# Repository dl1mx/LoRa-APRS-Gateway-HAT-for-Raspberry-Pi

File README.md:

What is it?
-----------
With this LoRa APRS board you can build a LoRa APRS single channel Gateway with RA-01.  
The Board is based on the development of https://www.lora-aprs.at/ and http://www.iot4pi.com/  
It works with a Raspberry Pi (2 Model B, 3 Model B an B+, Zero WH).  
Power is provided by Raspberry Pi.

What you find here
------------------
- KiCad Fils
- Gerber Files
- Manuals
- Pictures of the LoRa-APRS-Board

Info & Software
---------------
You find information and Software for the LoRa-APRS Gateway at  
https://www.aronaut.at/2019/11/lora-aprs-gateway-fur-raspberry-pi/  
https://www.lora-aprs.at/  
http://www.iot4pi.com/de/hardware/lora-gateway/  
https://github.com/tomelec/RPi-LoRa-KISS-TNC

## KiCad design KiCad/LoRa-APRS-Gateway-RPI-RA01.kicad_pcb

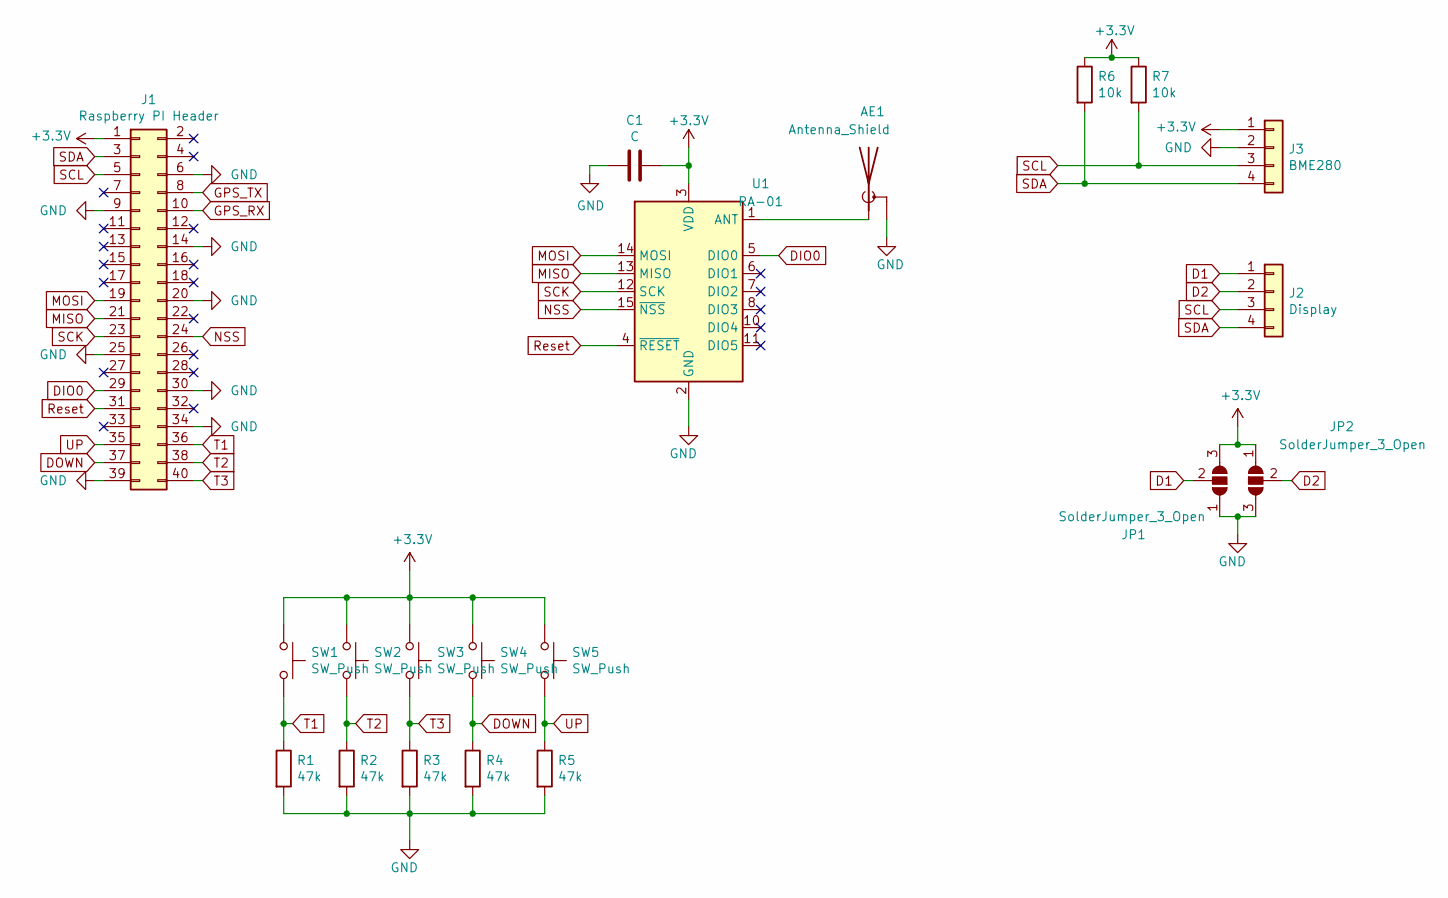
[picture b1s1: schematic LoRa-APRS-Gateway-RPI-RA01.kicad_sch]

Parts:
AE1: Antenna_Shield; SMA_Amphenol_901-144_Vertical
C1: C; C_0805_2012Metric
J1: Raspberry PI Header; PinSocket_2x20_P2.54mm_Vertical
J2: Display; OLED_0,96_II
J3: BME280; PinHeader_1x04_P2.54mm_Vertical
JP1, JP2: SolderJumper_3_Open; SolderJumper-3_P1.3mm_Open_Pad1.0x1.5mm
R1, R2, R3, R4, R5: 47k; R_Axial_DIN0207_L6.3mm_D2.5mm_P7.62mm_Horizontal
R6, R7: 10k; R_Axial_DIN0207_L6.3mm_D2.5mm_P7.62mm_Horizontal
SW1, SW2, SW3, SW4, SW5: SW_Push; SW_PUSH_6mm_H5mm
U1: RA-01; Ai-Thinker-Ra-01-LoRa

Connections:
+3.3V: C1.1, J1.1, J3.1, JP1.3 (B), JP2.1 (A), R6.1, R7.1, SW1.1, SW2.1, SW3.1, SW4.1, SW5.1, U1.3 (VDD)
D1: J2.1, JP1.2 (C)
D2: J2.2, JP2.2 (C)
DIO0: J1.29, U1.5 (DIO0)
DOWN: J1.37, R4.1, SW4.2
GND: AE1.2 (Shield), C1.2, J1.6, J1.9, J1.14, J1.20, J1.25, J1.30, J1.34, J1.39, J3.2, JP1.1 (A), JP2.3 (B), R1.2, R2.2, R3.2, R4.2, R5.2, U1.2 (GND), U1.9 (GND), U1.16 (GND)
GPS_RX: J1.10
GPS_TX: J1.8
MISO: J1.21, U1.13 (MISO)
MOSI: J1.19, U1.14 (MOSI)
NSS: J1.24, U1.15 (~NSS)
unnamed: AE1.1 (A), U1.1 (ANT)
Reset: J1.31, U1.4 (~RESET)
SCK: J1.23, U1.12 (SCK)
SCL: J1.5, J2.3, J3.3, R7.2
SDA: J1.3, J2.4, J3.4, R6.2
T1: J1.36, R1.1, SW1.2
T2: J1.38, R2.1, SW2.2
T3: J1.40, R3.1, SW3.2
UP: J1.35, R5.1, SW5.2

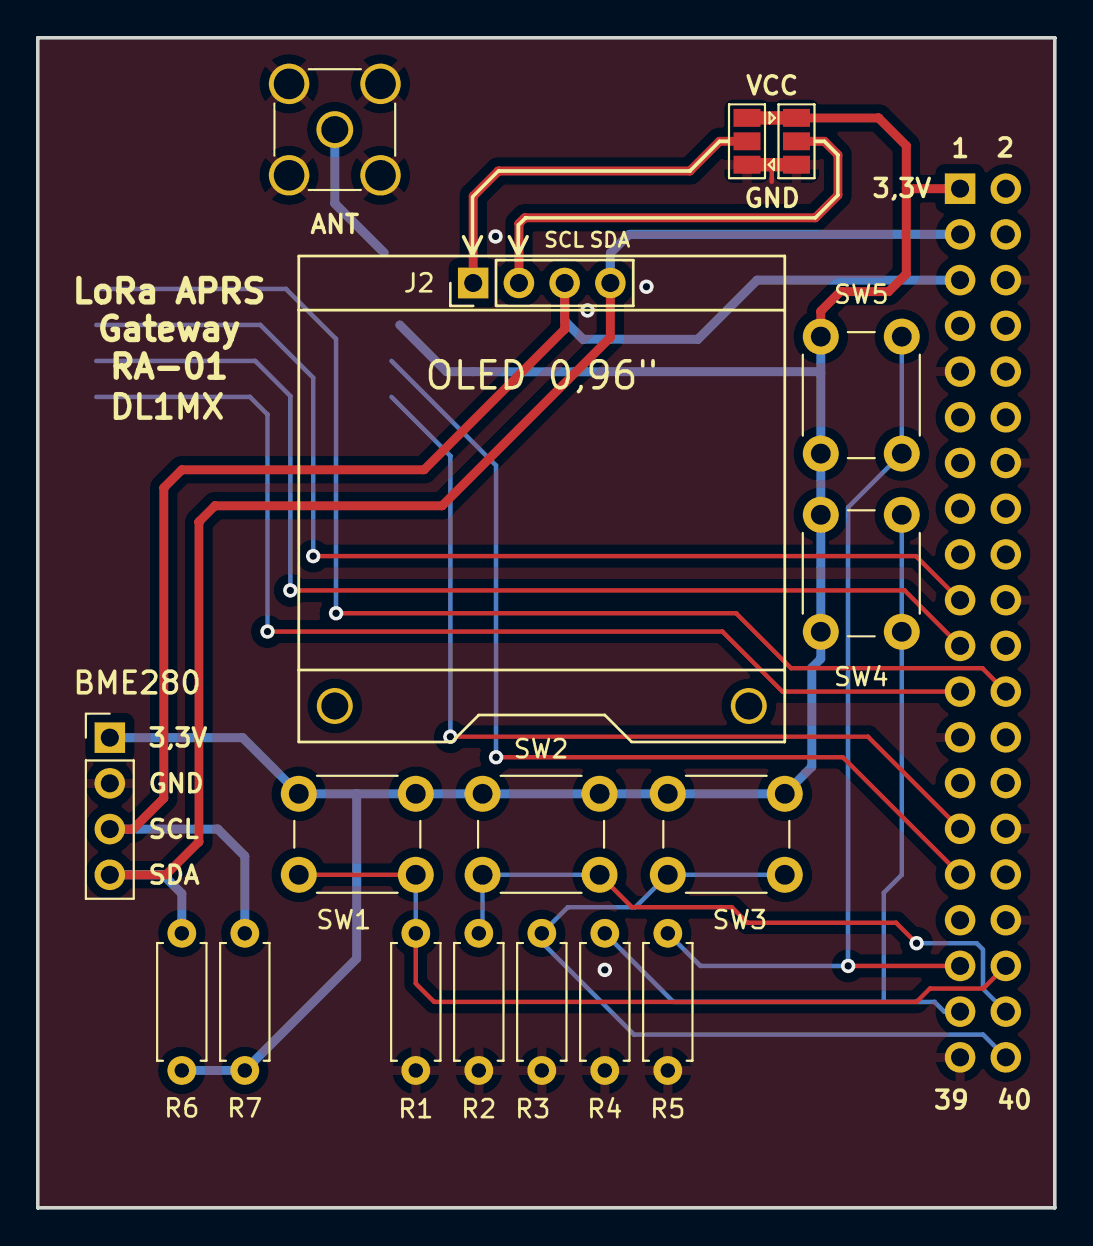
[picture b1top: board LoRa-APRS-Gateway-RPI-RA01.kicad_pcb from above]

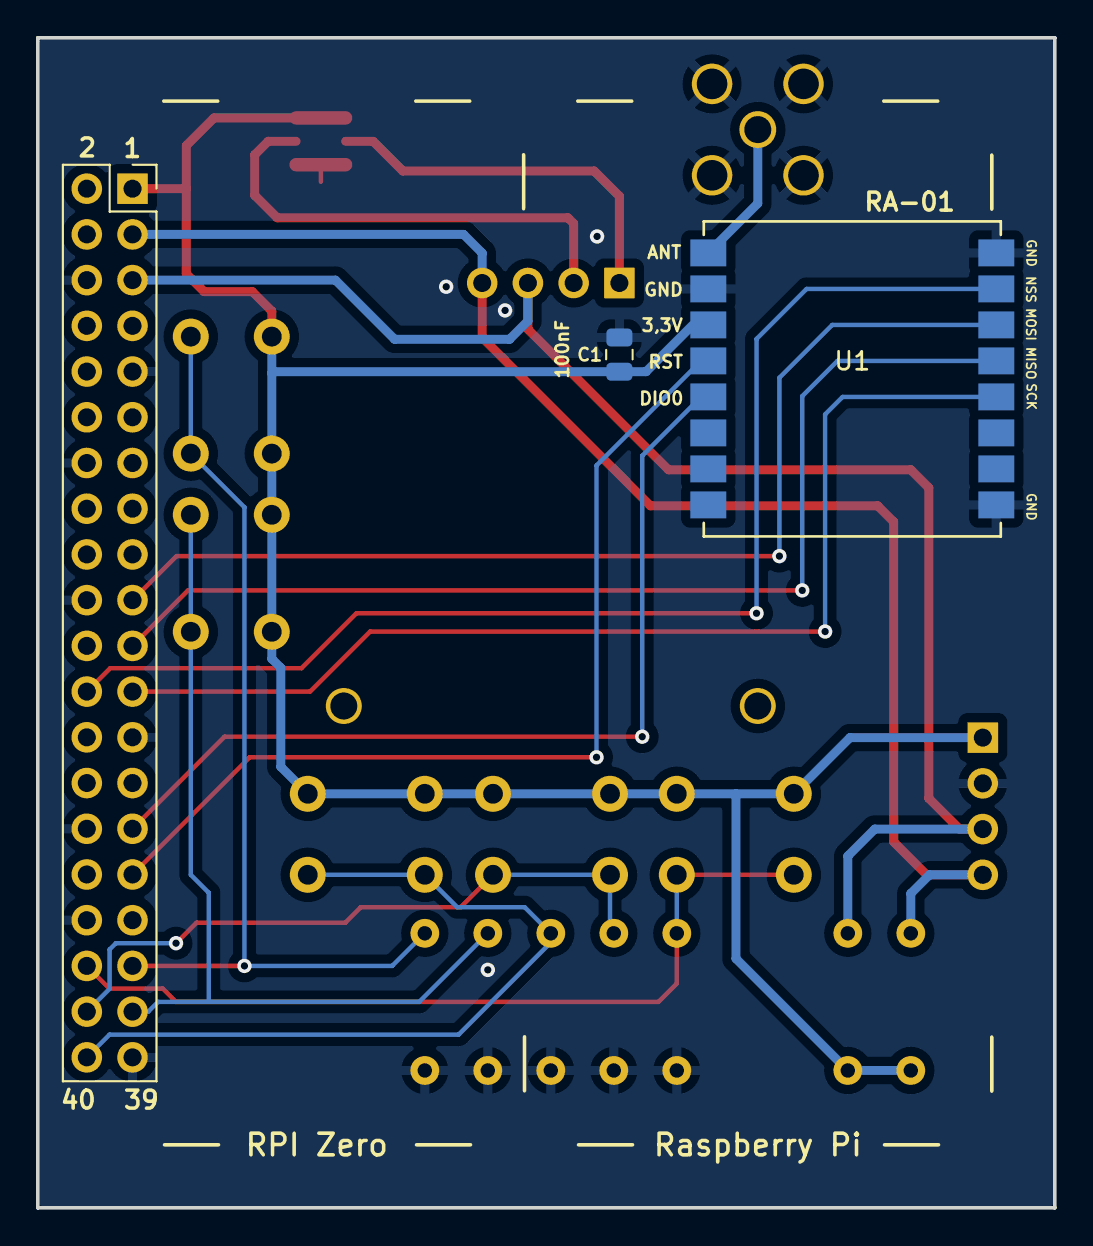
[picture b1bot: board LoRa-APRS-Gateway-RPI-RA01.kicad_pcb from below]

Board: 2 copper layers, 56.5 x 65.0 mm, 20 parts (3 on the bottom side), 18 nets.

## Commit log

2024-02-01 Changed radio chip to Ai-Thinker RA-01
2024-02-01 added new files
2024-02-01 added gerber files
2024-02-01 added new pictures
2024-02-01 added 3D pictures of board
